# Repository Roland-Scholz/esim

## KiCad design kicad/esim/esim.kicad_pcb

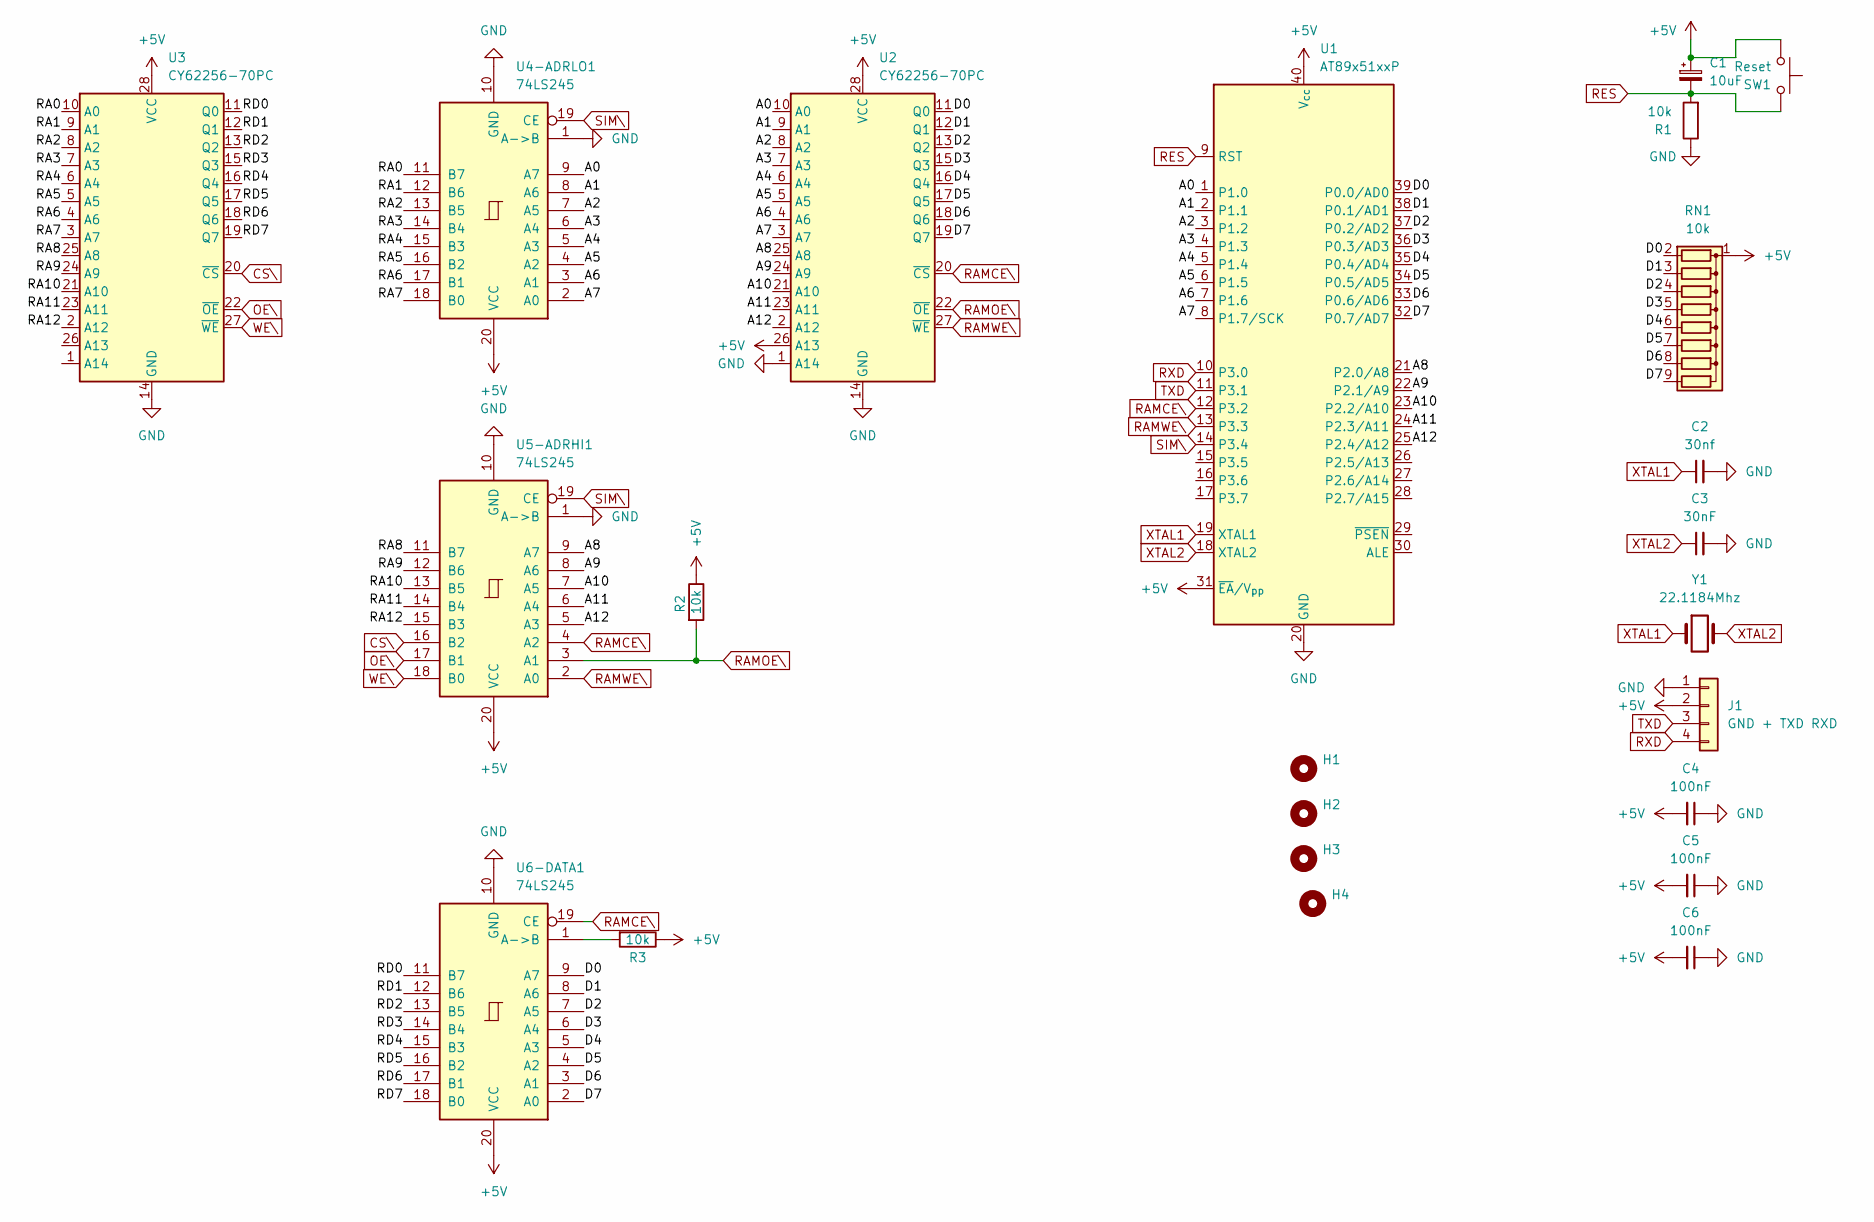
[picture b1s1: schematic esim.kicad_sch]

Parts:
C1: 10uF; CP_Radial_D5.0mm_P2.50mm
C2: 30nf; C_Disc_D3.0mm_W1.6mm_P2.50mm
C3: 30nF; C_Disc_D3.0mm_W1.6mm_P2.50mm
C4, C5, C6: 100nF; C_Disc_D5.0mm_W2.5mm_P5.00mm
H1, H2, H3, H4: MountingHole_5.3mm_M5_DIN965
J1: GND + TXD RXD; PinHeader_1x04_P2.54mm_Vertical
R1, R2, R3: 10k; R_Axial_DIN0204_L3.6mm_D1.6mm_P7.62mm_Horizontal
RN1: 10k; R_Array_SIP9
SW1: Reset; SW_PUSH_6mm
U1: AT89x51xxP; DIP-40_W15.24mm
U2, U3: CY62256-70PC; DIP-28_W15.24mm
U4-ADRLO1, U5-ADRHI1, U6-DATA1: 74LS245; DIP-20_W7.62mm_LongPads
Y1: 22.1184Mhz; Crystal_HC49-U_Vertical

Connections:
+5V: C1.1, C4.2, C5.2, C6.2, J1.2, R2.1, R3.1, RN1.1 (common), SW1.1, U1.31 (~EA/V_{pp}), U1.40 (V_{cc}), U2.26 (A13), U2.28 (VCC), U3.28 (VCC), U4-ADRLO1.20 (VCC), U5-ADRHI1.20 (VCC), U6-DATA1.20 (VCC)
/A0: U1.1 (P1.0), U2.10 (A0), U4-ADRLO1.9 (A7)
/A1: U1.2 (P1.1), U2.9 (A1), U4-ADRLO1.8 (A6)
/A2: U1.3 (P1.2), U2.8 (A2), U4-ADRLO1.7 (A5)
/A3: U1.4 (P1.3), U2.7 (A3), U4-ADRLO1.6 (A4)
/A4: U1.5 (P1.4), U2.6 (A4), U4-ADRLO1.5 (A3)
/A5: U1.6 (P1.5), U2.5 (A5), U4-ADRLO1.4 (A2)
/A6: U1.7 (P1.6), U2.4 (A6), U4-ADRLO1.3 (A1)
/A7: U1.8 (P1.7/SCK), U2.3 (A7), U4-ADRLO1.2 (A0)
/A8: U1.21 (P2.0/A8), U2.25 (A8), U5-ADRHI1.9 (A7)
/A9: U1.22 (P2.1/A9), U2.24 (A9), U5-ADRHI1.8 (A6)
/A10: U1.23 (P2.2/A10), U2.21 (A10), U5-ADRHI1.7 (A5)
/A11: U1.24 (P2.3/A11), U2.23 (A11), U5-ADRHI1.6 (A4)
/A12: U1.25 (P2.4/A12), U2.2 (A12), U5-ADRHI1.5 (A3)
/D0: RN1.2 (R1), U1.39 (P0.0/AD0), U2.11 (Q0), U6-DATA1.9 (A7)
/D1: RN1.3 (R2), U1.38 (P0.1/AD1), U2.12 (Q1), U6-DATA1.8 (A6)
/D2: RN1.4 (R3), U1.37 (P0.2/AD2), U2.13 (Q2), U6-DATA1.7 (A5)
/D3: RN1.5 (R4), U1.36 (P0.3/AD3), U2.15 (Q3), U6-DATA1.6 (A4)
/D4: RN1.6 (R5), U1.35 (P0.4/AD4), U2.16 (Q4), U6-DATA1.5 (A3)
/D5: RN1.7 (R6), U1.34 (P0.5/AD5), U2.17 (Q5), U6-DATA1.4 (A2)
/D6: RN1.8 (R7), U1.33 (P0.6/AD6), U2.18 (Q6), U6-DATA1.3 (A1)
/D7: RN1.9 (R8), U1.32 (P0.7/AD7), U2.19 (Q7), U6-DATA1.2 (A0)
/RA0: U3.10 (A0), U4-ADRLO1.11 (B7)
/RA1: U3.9 (A1), U4-ADRLO1.12 (B6)
/RA2: U3.8 (A2), U4-ADRLO1.13 (B5)
/RA3: U3.7 (A3), U4-ADRLO1.14 (B4)
/RA4: U3.6 (A4), U4-ADRLO1.15 (B3)
/RA5: U3.5 (A5), U4-ADRLO1.16 (B2)
/RA6: U3.4 (A6), U4-ADRLO1.17 (B1)
/RA7: U3.3 (A7), U4-ADRLO1.18 (B0)
/RA8: U3.25 (A8), U5-ADRHI1.11 (B7)
/RA9: U3.24 (A9), U5-ADRHI1.12 (B6)
/RA10: U3.21 (A10), U5-ADRHI1.13 (B5)
/RA11: U3.23 (A11), U5-ADRHI1.14 (B4)
/RA12: U3.2 (A12), U5-ADRHI1.15 (B3)
/RD0: U3.11 (Q0), U6-DATA1.11 (B7)
/RD1: U3.12 (Q1), U6-DATA1.12 (B6)
/RD2: U3.13 (Q2), U6-DATA1.13 (B5)
/RD3: U3.15 (Q3), U6-DATA1.14 (B4)
/RD4: U3.16 (Q4), U6-DATA1.15 (B3)
/RD5: U3.17 (Q5), U6-DATA1.16 (B2)
/RD6: U3.18 (Q6), U6-DATA1.17 (B1)
/RD7: U3.19 (Q7), U6-DATA1.18 (B0)
CS\: U3.20 (~CS), U5-ADRHI1.16 (B2)
GND: C2.2, C3.2, C4.1, C5.1, C6.1, J1.1, R1.1, U1.20 (GND), U2.1 (A14), U2.14 (GND), U3.14 (GND), U4-ADRLO1.1 (A->B), U4-ADRLO1.10 (GND), U5-ADRHI1.1 (A->B), U5-ADRHI1.10 (GND), U6-DATA1.10 (GND)
unnamed: R3.2, U6-DATA1.1 (A->B)
OE\: U3.22 (~OE), U5-ADRHI1.17 (B1)
RAMCE\: U1.12 (P3.2), U2.20 (~CS), U5-ADRHI1.4 (A2), U6-DATA1.19 (CE)
RAMOE\: R2.2, U2.22 (~OE), U5-ADRHI1.3 (A1)
RAMWE\: U1.13 (P3.3), U2.27 (~WE), U5-ADRHI1.2 (A0)
RES: C1.2, R1.2, SW1.2, U1.9 (RST)
RXD: J1.4, U1.10 (P3.0)
SIM\: U1.14 (P3.4), U4-ADRLO1.19 (CE), U5-ADRHI1.19 (CE)
TXD: J1.3, U1.11 (P3.1)
WE\: U3.27 (~WE), U5-ADRHI1.18 (B0)
XTAL1: C2.1, U1.19 (XTAL1), Y1.1
XTAL2: C3.1, U1.18 (XTAL2), Y1.2

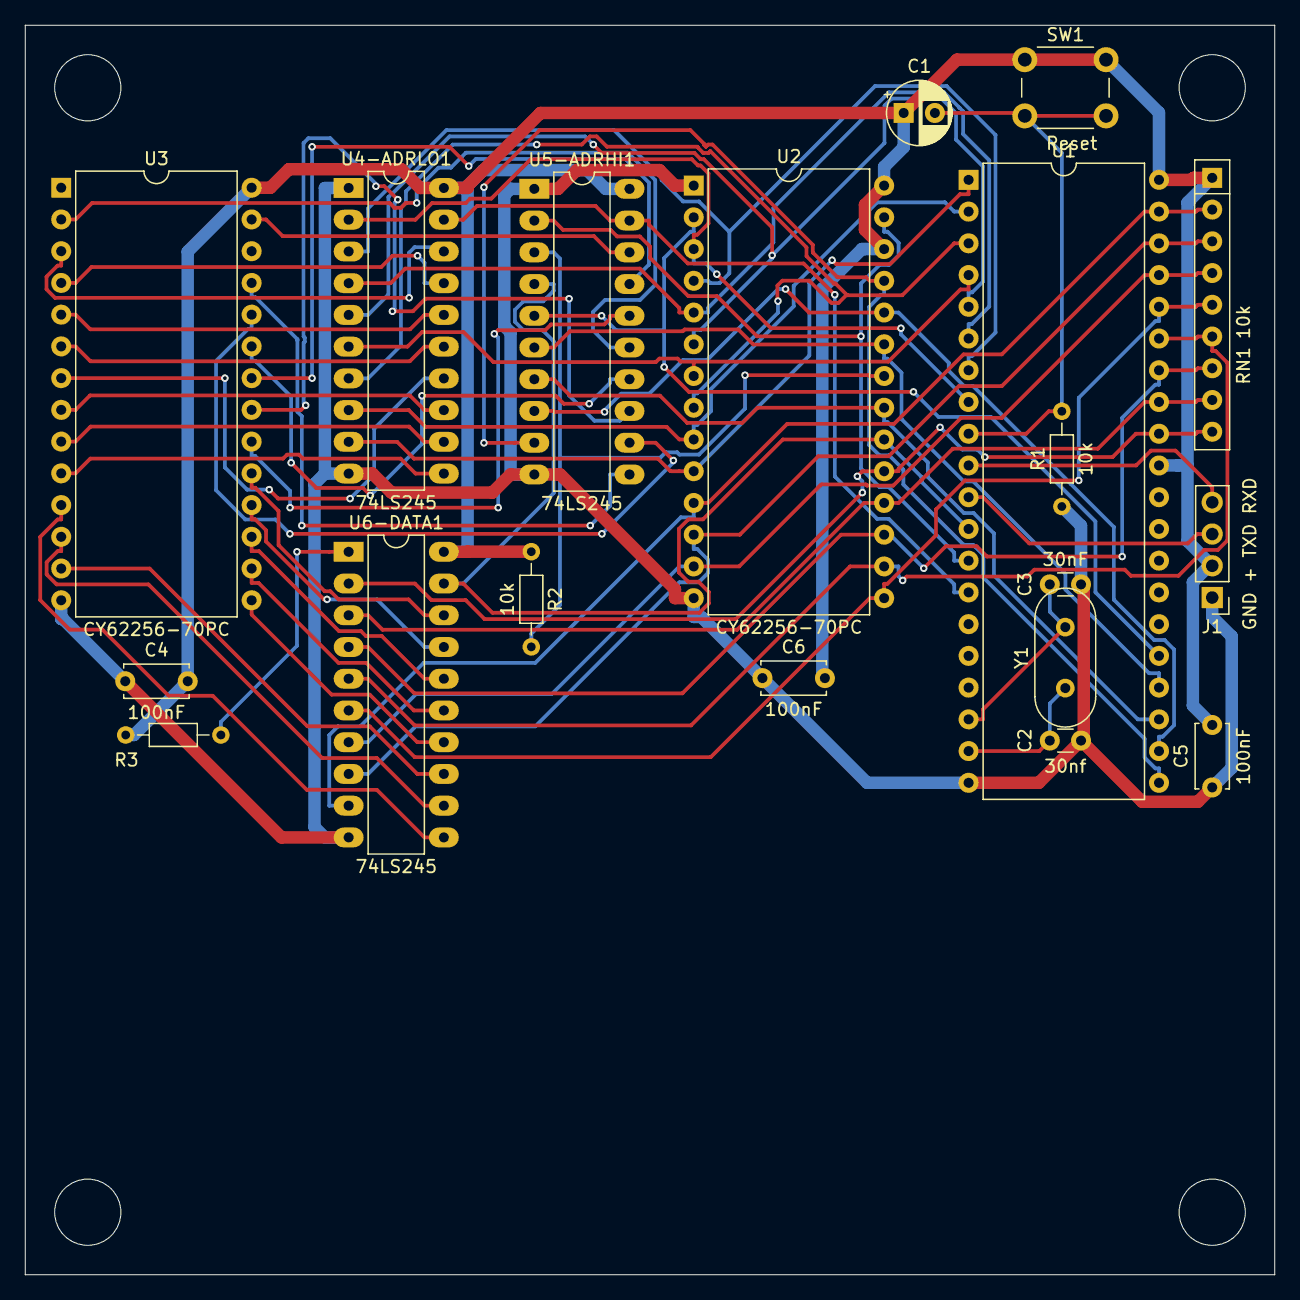
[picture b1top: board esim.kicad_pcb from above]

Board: 2 copper layers, 100.0 x 100.0 mm, 23 parts (0 on the bottom side), 57 nets.

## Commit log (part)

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2024-07-31 .gitignore
2024-07-31 esim pcb
2024-08-01 Rolli-1 Monitor
2024-08-04 Rolli
2024-08-09 Esim 8k MK2
2024-08-31 shorter code
